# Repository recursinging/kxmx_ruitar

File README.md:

# kxmx_ruitar

A guitar shaped MIDI/OSC instrument

## The Idea

The goal of this project is pretty simple; Take the general functionality of your typical MIDI keyboard or control surface and implement it (robustly, and with low latency) in the form factor of a guitar.  The motivation is a a little less straightforward. Three things:

1. I wanted to wear it on stage while maintaining the freedom to move about.  
1. I wanted to make it myself.
1. It didn't want to spend a fortune.

I like the form factor of a guitar because it can look quite traditional in a rock band context, but upon closer inspection is clearly not.  This reflects my taste in music, superficially recognizable, but substantially deviant.  While I can play the guitar, I didn't feel it necessary that a functional [guitar be augmented](http://lividinstruments.com/products/guitar-wing/) with MIDI controller capabilities, unless the two can be [seamlessly combined](https://www.rorguitars.com/products/expressiv-midi-pro). This is primarily because my single-threaded brain just cannot effectively handle playing an instrument well, while controlling other parameters. 

Because a guitar hangs down in front of you, facing out, visual controls and feedback are pretty useless.  [A touch screen on the front of the guitar](https://misa-digital.myshopify.com/products/tri-bass) for example, is effectively a touch-pad for the player and a light show for the audience. Therefore I am mostly interested in tactile type sensors which can be blindly interacted with.

The DIY approach is simply an excuse to get lost in the details of interesting technical challenges instead of practicing, or composing actual music. 

Regarding limiting cost... Yeah, anyone who has ever attempted a DIY project like this knows it's actually BS. There is no competing with the economies of scale that a market product has. We DIYers like to trick ourselves by spreading the costs into tiny chunks, over many months. But, I consider the premium an investment in enjoyment and the knowledge gained along the way. So that's how it ended up here.  

## The (current) BOM

* 1 [Teensy 3.6](https://www.pjrc.com/store/teensy36.html) with SD card
* 1 Junk electric guitar, or similarly shaped object.
* 4 500mm [ThinPot](http://www.spectrasymbol.com/product/thinpot/) Membrane Potentiometers (Strings)
* 4 38x38mm [FSR](https://www.interlinkelectronics.com/fsr-406) Pressure Sensors (Pads)
* 1 [Joystick](https://www.adafruit.com/product/444)
* 4 45mm [Slider Potentiometers](https://www.digikey.com/product-detail/en/tt-electronics-bi/PS45-21PC3BR10K/987-1409-ND/2620678) (Faders)
* 4 [LED Buttons](https://www.sparkfun.com/products/10442) (Toggles)
* 1 [SSD1306 64x32 OLED display](https://www.adafruit.com/product/326)
* A diverse set of 0805 SMD resistors and capacitors
* Bits and Bobs (proto board, hookup wire, solder, tape, velcro, etc.)

(With Optional Headstock)

* 1 [Teensy LC](https://www.pjrc.com/teensy/teensyLC.html)
* 4 [RGB LED Rotary Encoders](https://www.sparkfun.com/products/10982)
* 1 [ADXL345 3 Axis Accelerometer](https://www.sparkfun.com/datasheets/Sensors/Accelerometer/ADXL345.pdf) (Accel)
* 1 [TLC5940 PWM Controller](http://www.ti.com/lit/ds/symlink/tlc5940.pdf)
* A diverse set of 0805 SMD resistors and capacitors
* [The ruitar-head PCB]()

## The Build

The guitar used was a junk no-name electric.  I hollowed out from the front of the body with an oscillating multi-tool and a wood blade, leaving space for the FSRs.  Because the body is plywood, it was pretty easy to remove the bulk of the material.  I spray-painted everything black and carpeted the inside with adhesive Velcro strips (loop side). This has been quite helpful for cable management and general experimentation.  Just put some hook Velcro to the bottom of a breadboard and stick it in there. Need a USB Hub? Raspberry Pi? Velcro!

The FSRs are attached with some double sided foam tape which holds them solidly in place and gives them a little bit of padding, which is good when you are banging on them with your knuckles.  The little thumb joystick is mounted in the body with hot glue, and wired through a hole bored into the body cavity. The joystick is meant to be moved with the palm of your hand, allowing you to modulate parameters while tapping on the FSRs... In practice, little thumb joysticks like that are junk, they have too little travel to introduce any decent dynamic.  I am actively looking for an alternative, larger joystick with more travel.

The first prototype was done using breadboards and an Arduino Mega2650 clone.  When it was finally functional, I found the latency to be unacceptable, the breadboard connections were fragile and problematic,and I also found it lacking interface components.  So, I swapped the Mega2650 for a Teensy 3.6, soldered all the connections using some protoboard, and added the four faders plus four LED buttons. The result is this new prototype module. I'm designing a PCB which will replace this.

There are USB-A and RJ-45 jacks to the side using some nice, locking Neutrik jacks.  Because the Teensy's advanced USB capabilities, there is only USB IO at the moment.  The unused RJ-45 is for some future ideas.

There is an SSD1306 64x32 OLED display mounted to the side of the body of the guitar. I simply flattened a little part of the edge with a belt sander, and drilled a hole into the body cavity for the wires. A 3d-printed protective case surrounding the display would be useful.

There is a cover for the body cavity I cut out of plastic to hide the unruly guts (although the aesthetics of the exposed internals are also appealing).  Note that this photo was also taken before the faders and buttons were added, which means that the cover, in that form is not currently usable, but I'm still unsure about the final positions of those components anyhow. 

The neck was a huge pain. Removing the truss rod required brute force, but afterward I had a cable channel through which I am able to pull wires from the body, up to the head stock. In order to adhere the membrane potentiometers, I needed to flatten the fingerboard. I didn't have any good ideas how, so I ended up just sanding the frets down with a belt sander. There are no photos of this process because I was too busy cursing. The result is OK but if you want to try this yourself, I'd recommend looking for a cheap neck without a fingerboard (although I was unable to find one). Once flattened I attached the membrane potentiometers and covered them with a layer of electrical tape.  I then laid some straightened 14 gauge solid core wire down the middle of each sensor, and put another layer of tape on top.  This provides some tactile feedback as to where the sensors actually are, and really helps the play-ability.  The position tracking through the wire is excellent.

[The headstock](https://github.com/recursinging/kxmx_ruitar/tree/master/ruitar-head) is a separate entity with its own microcontroller, a ([Teensy LC](https://www.pjrc.com/teensy/teensyLC.html)) acting as an I²C slave device.  It is attached to the headstock of a guitar. I've connected it to the body module with wires pulled through the neck of the guitar.  I removed all the tuning hardware and screwed it directly to the headstock.  Currently, it is quite exposed and fragile.  I'd like to design a 3d printed protective cover for it.

Put all together and you have a ruitar!

## Schematics

TODO

## Firmware

Because the headstock and body have their own microcontrollers, this project is split into two sections, the *ruitar-body* and the *ruitar-head*.  The directory layouts of both projects are currently set up for [platformio](https://platformio.org/), it works. It's not bad.

### [ruitar-body](https://github.com/recursinging/kxmx_ruitar/tree/master/ruitar-head)

The ruitar-body is the core of the instrument, effectively a variety of sensors attached to a microcontroller (a [Teensy 3.6](https://www.pjrc.com/store/teensy36.html)).  These sensors are sampled via the microcontroller ADCs, the values are calculated and, if appropriate, MIDI and OSC messages are sent out. (currently via USB to a PC).

The logic controlling when and what messages to send is configurable by a INI style text files on an SD card. These files can be considered "Presets" and can be copied, modified, renamed, and saved to the SD card.  

TODO - Include config file example

I had plans to make presets configurable through the sensors, and OLED display, but I found the OSC GUI much easier and more powerful, so the OLED display is currently relegated to display some basic debugging info at the moment.  Perhaps there is a better use for it, or the SPI pins it is occupying?

Presets can also be edited via OSC using [the GUI definition](https://github.com/recursinging/kxmx_ruitar/blob/master/osc-gui.json) for [Open Stage Control](https://osc.ammd.net/)

The default configuration is for it to behave a bit like a real guitar. Pressing a position on a "string" (0-3) determines the pitch of the note, while triggering the note on state, and its velocity is determined by pressure detected at the associated (0-3) "pad".  The faders, and toggles emit CC messages, and the joystick can emit CC and pitch bend messages. Sensor values received from the head (accelerometer, encoders) can also be configured to emit MIDI CC messages.

### [ruitar-head](https://github.com/recursinging/kxmx_ruitar/tree/master/ruitar-head)

The ruitar-head is set of sensors attached to a microcontroller ([Teensy LC](https://www.pjrc.com/teensy/teensyLC.html)) acting as an I²C slave device. The firmware provides a set of read-only registers which can be read to obtain the accelerometer, and encoder values.  Additionally the state of the RGB LEDs can be polled and changed by a set of read-write registers.

## TODOs

Things that still need to be done, but are incomplete.

- [ ] Design a PCB for the body
- [ ] Fix broken I²C communication between body and head
- [ ] Implement the OSC GUI parameter config
- [ ] Implement the OSC GUI preset copy/rename/save functions
- [ ] Implement a useful MIDI emitter for the accelerometer data
- [ ] Design some 3d printable protective parts for the exposed bits.
- [ ] Provide better descriptions, code comments, build docs, pics, etc

## Future Feature Ideas

A few ideas I've been batting around:

### Synth! 

The Teensy 3.6 is laughing at the current workload.  There is plenty of capacity to implement a digital synth, and the Teensy Audio library is amazing.  I've already started this, but ran into a couple of problems:

* An I²S codec needs quite a few pins, many of which are currently being used
* USB audio is not really an option if you already have a USB audio interface.

Nothing insurmountable, I'd like to make this happen if I find the time.

### Ethernet (or WiFi)

At the moment OSC is provided over SLIP encoded Serial. This works, but is a kludge requiring [a bridge program](https://github.com/recursinging/kxmx_trestle) to get the UDP packets that all the OSC clients expect.

There is a Neutrik RJ-45 jack built into the body of the ruitar,  I could provide power over the unused pairs assuming 100-BASE-T.  But without the USB cable I would loose all the USB* devices the Teensy can emulate, which would be a bummer. 

Alternatively I could send the SLIP serial to an ESP32 and broadcast the OSC packets via WiFi, not sure about the latency though. 

### Membrane Potentiometer Alternatives

The kxmx_ruitar is *really* hard to play.  Tracking on the "strings" is not bad, but the lack of any tactile feedback along them makes it difficult to get a position reference. Anyway, since MIDI notes are discrete, all the position data the pot and ADC could provide gets quantized to the configured 20 note range anyway... They might as well be buttons, right?

## Inspiration, Ideas, and Prior Art

Here's a list of products and projects from which I have gathered ideas:

* [Misa Digital Tri-Bass](https://misa-digital.myshopify.com/products/tri-bass)
* [Starr Labs Z-Tars](https://www.starrlabs.com/product/z6s/)
* [Expressiv MIDI Pro](https://www.rorguitars.com/products/expressiv-midi-pro)
* [Alesis Vortex](https://www.alesis.com/products/view2/vortex-wireless-2)

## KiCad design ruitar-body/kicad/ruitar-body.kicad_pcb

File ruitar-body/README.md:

# kxmx_ruitar_body

The body module of the kxmx_ruitar

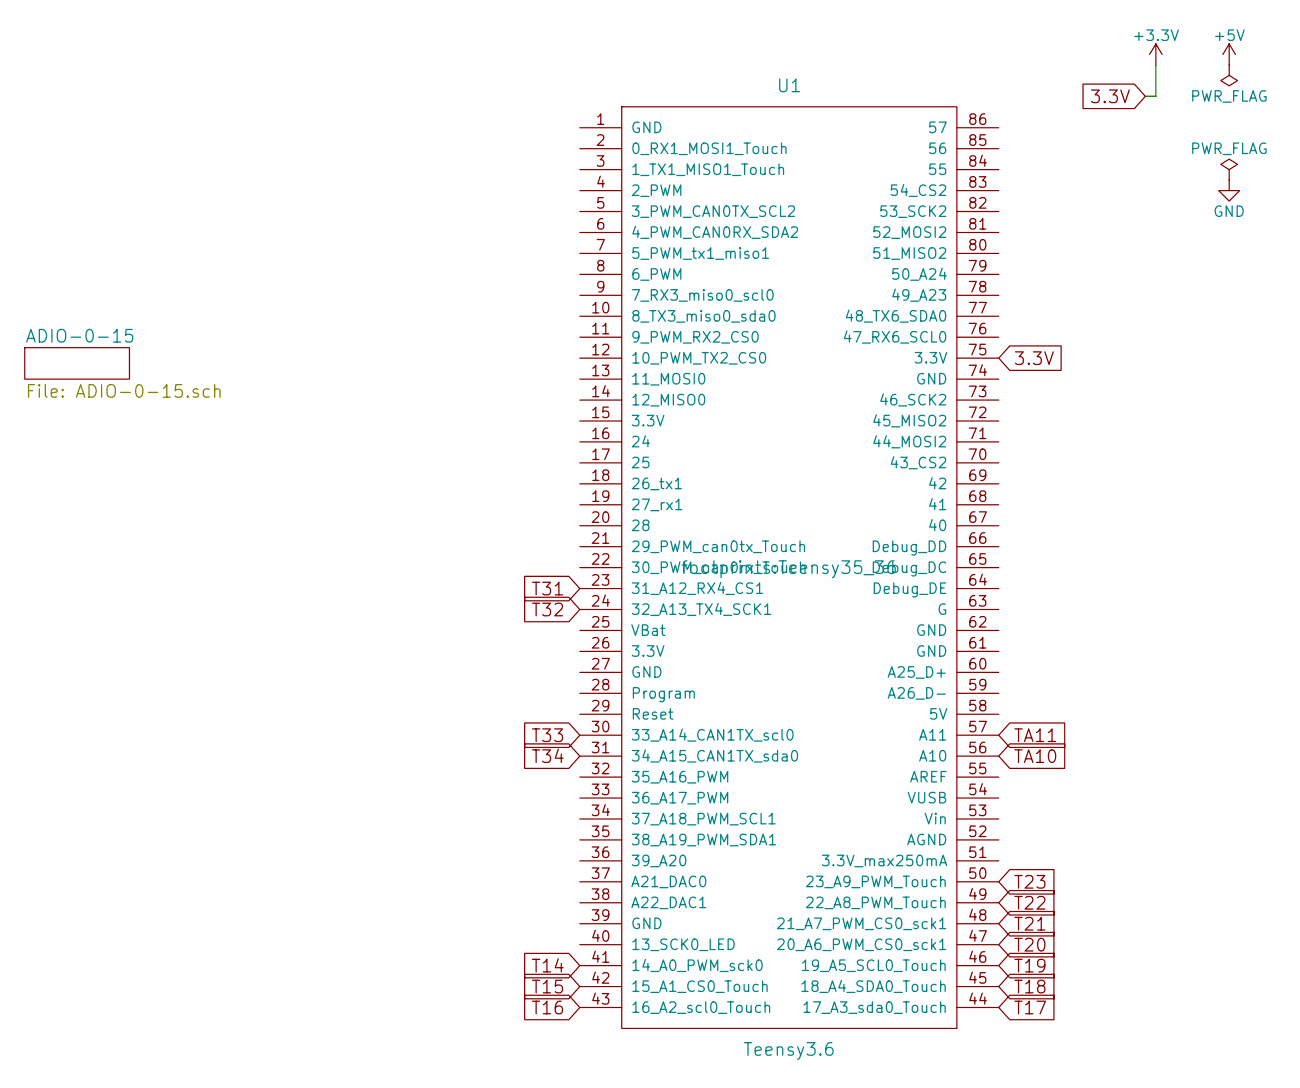
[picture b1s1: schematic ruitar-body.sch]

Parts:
U1: Teensy3.6; Teensy35_36

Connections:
3.3V: U1.75 (3.3V); also elsewhere on the board
T14: U1.41 (14_A0_PWM_sck0); also elsewhere on the board
T15: U1.42 (15_A1_CS0_Touch); also elsewhere on the board
T16: U1.43 (16_A2_scl0_Touch); also elsewhere on the board
T17: U1.44 (17_A3_sda0_Touch); also elsewhere on the board
T18: U1.45 (18_A4_SDA0_Touch); also elsewhere on the board
T19: U1.46 (19_A5_SCL0_Touch); also elsewhere on the board
T20: U1.47 (20_A6_PWM_CS0_sck1); also elsewhere on the board
T21: U1.48 (21_A7_PWM_CS0_sck1); also elsewhere on the board
T22: U1.49 (22_A8_PWM_Touch); also elsewhere on the board
T23: U1.50 (23_A9_PWM_Touch); also elsewhere on the board
T31: U1.23 (31_A12_RX4_CS1); also elsewhere on the board
T32: U1.24 (32_A13_TX4_SCK1); also elsewhere on the board
T33: U1.30 (33_A14_CAN1TX_scl0); also elsewhere on the board
T34: U1.31 (34_A15_CAN1TX_sda0); also elsewhere on the board
TA10: U1.56 (A10); also elsewhere on the board
TA11: U1.57 (A11); also elsewhere on the board

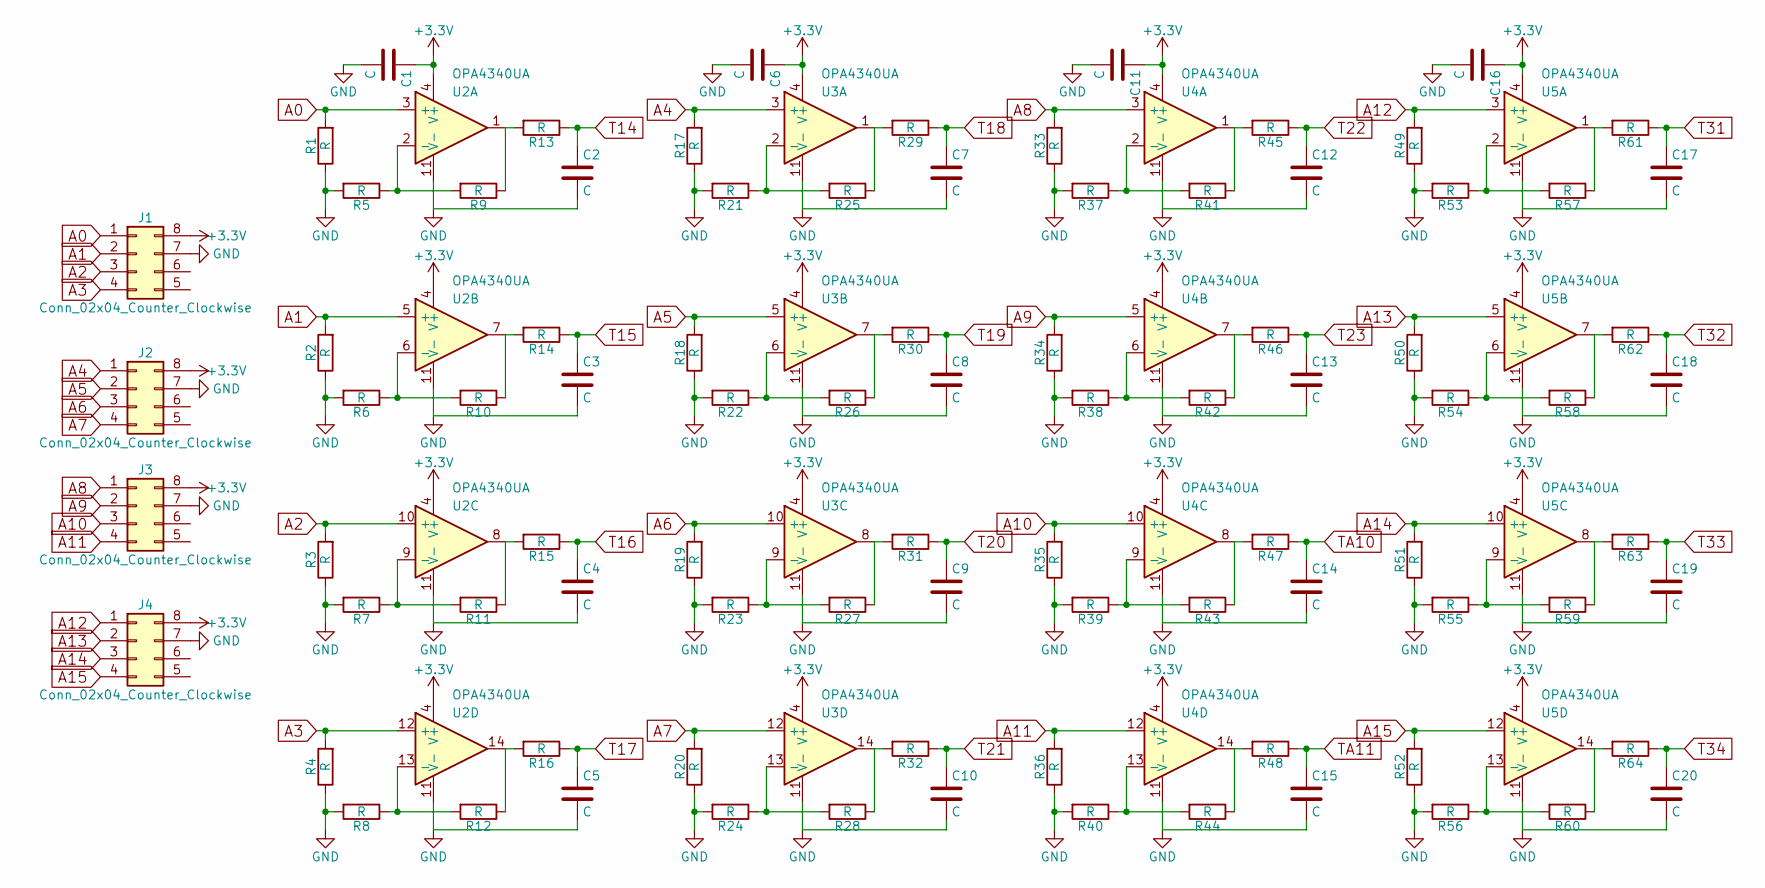
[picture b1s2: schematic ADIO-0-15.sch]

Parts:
C1, C2, C3, C4, C5, C6, C7, C8, C9, C10, C11, C12, C13, C14, C15, C16, C17, C18, C19, C20: C; C_0805
J1, J2, J3, J4: Conn_02x04_Counter_Clockwise; RJ45_8
R1, R2, R3, R4, R5, R6, R7, R8, R9, R10, R11, R12, R13, R14, R15, R16, R17, R18, R19, R20, R21, R22, R23, R24, R25, R26, R27, R28, R29, R30, R31, R32, R33, R34, R35, R36, R37, R38, R39, R40, R41, R42, R43, R44, R45, R46, R47, R48, R49, R50, R51, R52, R53, R54, R55, R56, R57, R58, R59, R60, R61, R62, R63, R64: R; R_0805
U2, U3, U4, U5: OPA4340UA; SOIC-14_3.9x8.7mm_Pitch1.27mm

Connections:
3.3V: C1.1, C6.1, C11.1, C16.1, J1.8, J2.8, J3.8, J4.8, U2.4 (V+), U3.4 (V+), U4.4 (V+), U5.4 (V+); also elsewhere on the board
A0: J1.1, R1.2, U2.3 (+)
A1: J1.2, R2.2, U2.5 (+)
A2: J1.3, R3.2, U2.10 (+)
A3: J1.4, R4.2, U2.12 (+)
A4: J2.1, R17.2, U3.3 (+)
A5: J2.2, R18.2, U3.5 (+)
A6: J2.3, R19.2, U3.10 (+)
A7: J2.4, R20.2, U3.12 (+)
A8: J3.1, R33.2, U4.3 (+)
A9: J3.2, R34.2, U4.5 (+)
A10: J3.3, R35.2, U4.10 (+)
A11: J3.4, R36.2, U4.12 (+)
A12: J4.1, R49.2, U5.3 (+)
A13: J4.2, R50.2, U5.5 (+)
A14: J4.3, R51.2, U5.10 (+)
A15: J4.4, R52.2, U5.12 (+)
GND: C1.2, C2.2, C3.2, C4.2, C5.2, C6.2, C7.2, C8.2, C9.2, C10.2, C11.2, C12.2, C13.2, C14.2, C15.2, C16.2, C17.2, C18.2, C19.2, C20.2, J1.7, J2.7, J3.7, J4.7, R1.1, R2.1, R3.1, R4.1, R5.2, R6.2, R7.2, R8.2, R17.1, R18.1, R19.1, R20.1, R21.2, R22.2, R23.2, R24.2, R33.1, R34.1, R35.1, R36.1, R37.2, R38.2, R39.2, R40.2, R49.1, R50.1, R51.1, R52.1, R53.2, R54.2, R55.2, R56.2, U2.11 (V-), U3.11 (V-), U4.11 (V-), U5.11 (V-)
unnamed: R5.1, R9.2, U2.2 (-)
unnamed: R10.1, R14.2, U2.7
unnamed: R6.1, R10.2, U2.6 (-)
unnamed: R11.1, R15.2, U2.8
unnamed: R7.1, R11.2, U2.9 (-)
unnamed: R12.1, R16.2, U2.14
unnamed: R8.1, R12.2, U2.13 (-)
unnamed: R9.1, R13.2, U2.1
unnamed: R21.1, R25.2, U3.2 (-)
unnamed: R22.1, R26.2, U3.6 (-)
unnamed: R23.1, R27.2, U3.9 (-)
unnamed: R24.1, R28.2, U3.13 (-)
unnamed: R25.1, R29.2, U3.1
unnamed: R26.1, R30.2, U3.7
unnamed: R27.1, R31.2, U3.8
unnamed: R28.1, R32.2, U3.14
unnamed: R37.1, R41.2, U4.2 (-)
unnamed: R38.1, R42.2, U4.6 (-)
unnamed: R39.1, R43.2, U4.9 (-)
unnamed: R40.1, R44.2, U4.13 (-)
unnamed: R41.1, R45.2, U4.1
unnamed: R42.1, R46.2, U4.7
unnamed: R43.1, R47.2, U4.8
unnamed: R44.1, R48.2, U4.14
unnamed: R53.1, R57.2, U5.2 (-)
unnamed: R54.1, R58.2, U5.6 (-)
unnamed: R55.1, R59.2, U5.9 (-)
unnamed: R56.1, R60.2, U5.13 (-)
unnamed: R57.1, R61.2, U5.1
unnamed: R58.1, R62.2, U5.7
unnamed: R59.1, R63.2, U5.8
unnamed: R60.1, R64.2, U5.14
T14: C2.1, R13.1; also elsewhere on the board
T15: C3.1, R14.1; also elsewhere on the board
T16: C4.1, R15.1; also elsewhere on the board
T17: C5.1, R16.1; also elsewhere on the board
T18: C7.1, R29.1; also elsewhere on the board
T19: C8.1, R30.1; also elsewhere on the board
T20: C9.1, R31.1; also elsewhere on the board
T21: C10.1, R32.1; also elsewhere on the board
T22: C12.1, R45.1; also elsewhere on the board
T23: C13.1, R46.1; also elsewhere on the board
T31: C17.1, R61.1; also elsewhere on the board
T32: C18.1, R62.1; also elsewhere on the board
T33: C19.1, R63.1; also elsewhere on the board
T34: C20.1, R64.1; also elsewhere on the board
TA10: C14.1, R47.1; also elsewhere on the board
TA11: C15.1, R48.1; also elsewhere on the board

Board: 2 copper layers, 93 parts (0 on the bottom side), 66 nets, no tracks yet.

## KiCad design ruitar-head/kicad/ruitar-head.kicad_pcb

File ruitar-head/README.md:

# kxmx_ruitar_head

The headstock module of the kxmx_ruitar

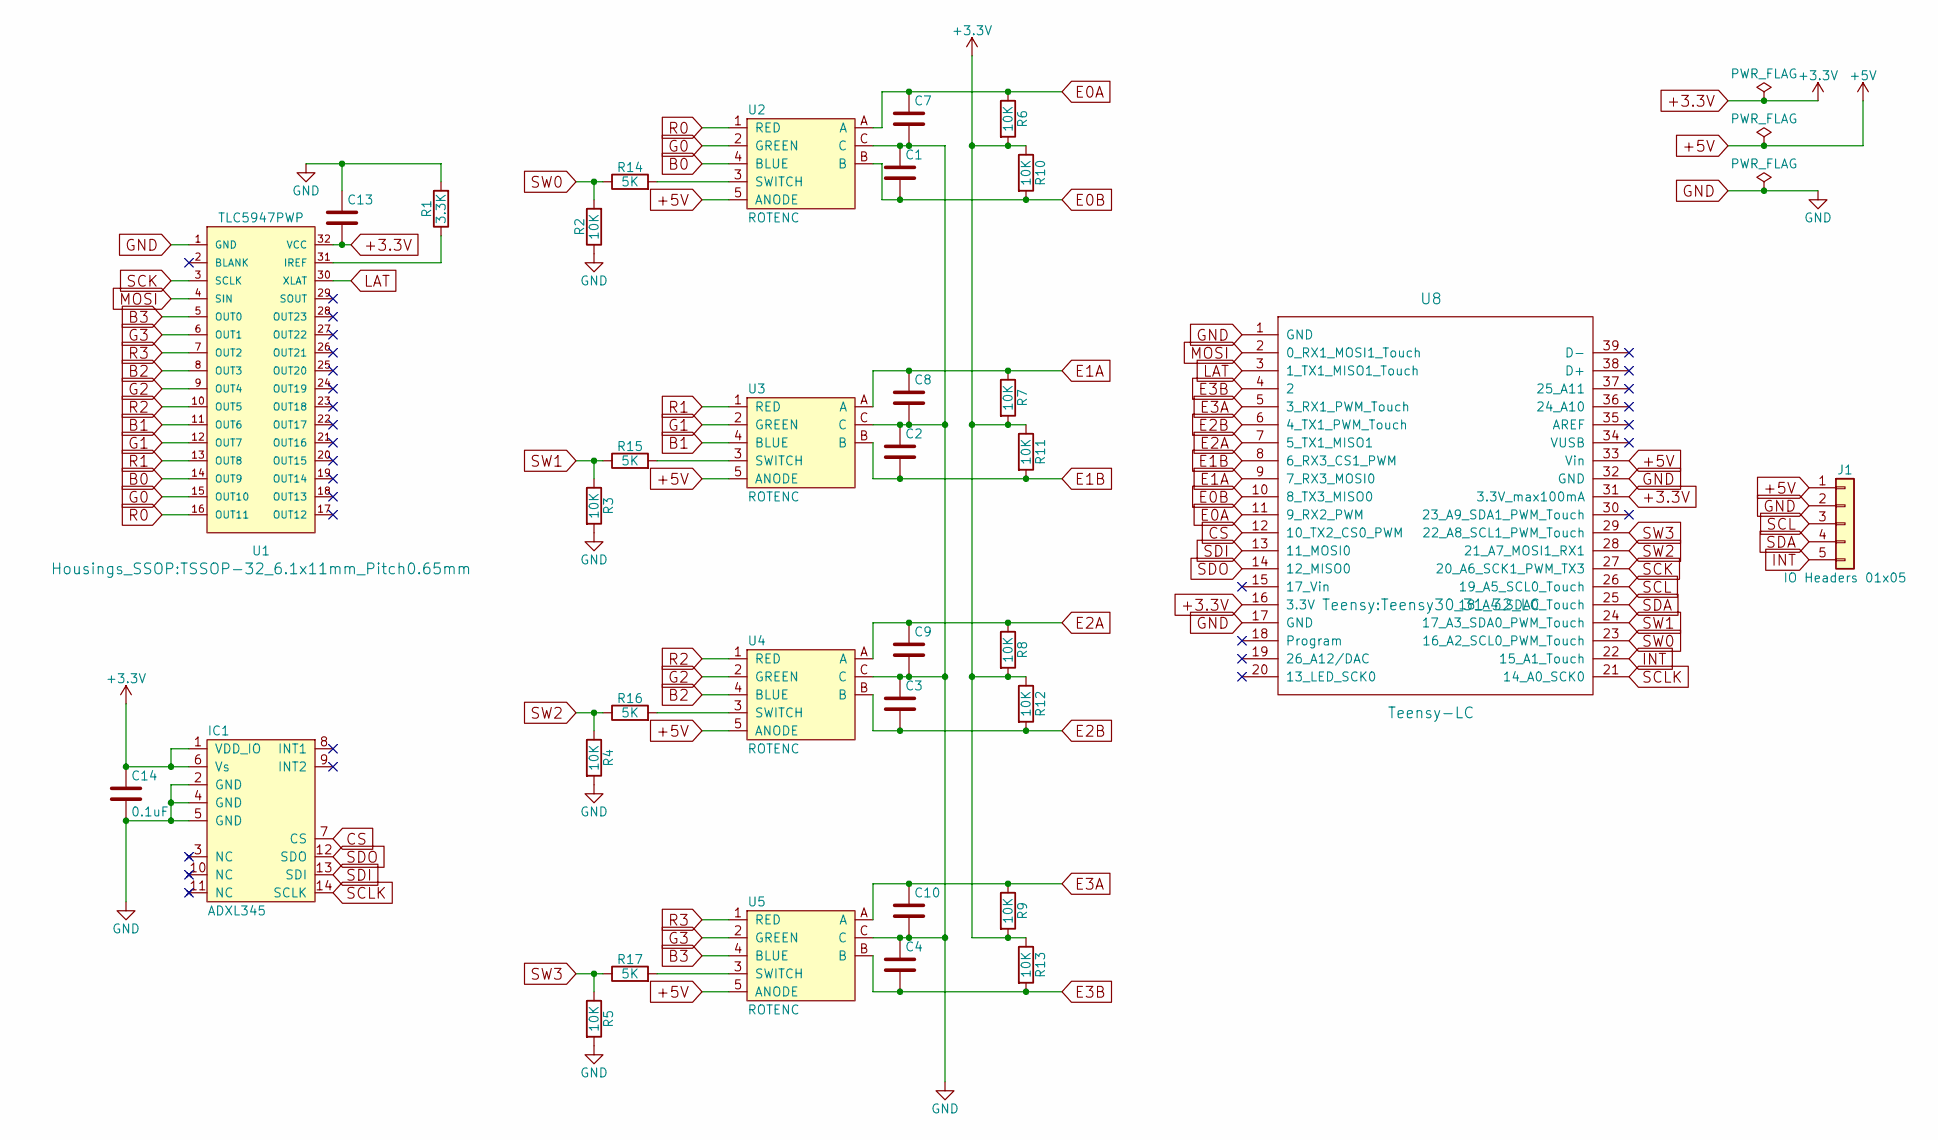
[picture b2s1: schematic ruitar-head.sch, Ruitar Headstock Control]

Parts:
C1, C2, C3, C4, C7, C8, C9, C10, C13, C14: 0.1uF; C_0805_HandSoldering
IC1: ADXL345; ADXL3x5; Farnell 1853935
J1: IO Headers 01x05; Pin_Header_Straight_1x05_Pitch2.54mm
R1: 3.3K; R_0805_HandSoldering
R2, R3, R4, R5, R6, R7, R8, R9, R10, R11, R12, R13: 10K; R_0805_HandSoldering
R14, R15, R16, R17: 5K; R_0805_HandSoldering
U1: TLC5947PWP; TSSOP-32_6.1x11mm_Pitch0.65mm
U2, U3, U4, U5: ROTENC; SF_ROTENC
U8: Teensy-LC; Teensy30_31_32_LC

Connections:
+3.3V: C13.2, C14.1, IC1.1 (VDD_IO), IC1.6 (Vs), R6.2, R7.2, R8.2, R9.2, R10.1, R11.1, R12.1, R13.1, U1.32 (VCC), U8.16 (3.3V), U8.31 (3.3V_max100mA)
+5V: J1.1, U2.5 (ANODE), U3.5 (ANODE), U4.5 (ANODE), U5.5 (ANODE), U8.33 (Vin)
B0: U1.14 (OUT9), U2.4 (BLUE)
B1: U1.11 (OUT6), U3.4 (BLUE)
B2: U1.8 (OUT3), U4.4 (BLUE)
B3: U1.5 (OUT0), U5.4 (BLUE)
CS: IC1.7 (CS), U8.12 (10_TX2_CS0_PWM)
E0A: C7.1, R6.1, U2.A, U8.11 (9_RX2_PWM)
E0B: C1.2, R10.2, U2.B, U8.10 (8_TX3_MISO0)
E1A: C8.1, R7.1, U3.A, U8.9 (7_RX3_MOSI0)
E1B: C2.2, R11.2, U3.B, U8.8 (6_RX3_CS1_PWM)
E2A: C9.1, R8.1, U4.A, U8.7 (5_TX1_MISO1)
E2B: C3.2, R12.2, U4.B, U8.6 (4_TX1_PWM_Touch)
E3A: C10.1, R9.1, U5.A, U8.5 (3_RX1_PWM_Touch)
E3B: C4.2, R13.2, U5.B, U8.4 (2)
G0: U1.15 (OUT10), U2.2 (GREEN)
G1: U1.12 (OUT7), U3.2 (GREEN)
G2: U1.9 (OUT4), U4.2 (GREEN)
G3: U1.6 (OUT1), U5.2 (GREEN)
GND: C1.1, C2.1, C3.1, C4.1, C7.2, C8.2, C9.2, C10.2, C13.1, C14.2, IC1.2 (GND), IC1.4 (GND), IC1.5 (GND), J1.2, R1.2, R2.1, R3.2, R4.2, R5.2, U1.1 (GND), U2.C, U3.C, U4.C, U5.C, U8.1 (GND), U8.17 (GND), U8.32 (GND)
INT: J1.5, U8.22 (15_A1_Touch)
LAT: U1.30 (XLAT), U8.3 (1_TX1_MISO1_Touch)
MOSI: U1.4 (SIN), U8.2 (0_RX1_MOSI1_Touch)
unnamed: R1.1, U1.31 (IREF)
unnamed: R14.2, U2.3 (SWITCH)
unnamed: R15.2, U3.3 (SWITCH)
unnamed: R16.2, U4.3 (SWITCH)
unnamed: R17.2, U5.3 (SWITCH)
R0: U1.16 (OUT11), U2.1 (RED)
R1: U1.13 (OUT8), U3.1 (RED)
R2: U1.10 (OUT5), U4.1 (RED)
R3: U1.7 (OUT2), U5.1 (RED)
SCK: U1.3 (SCLK), U8.27 (20_A6_SCK1_PWM_TX3)
SCL: J1.3, U8.26 (19_A5_SCL0_Touch)
SCLK: IC1.14 (SCLK), U8.21 (14_A0_SCK0)
SDA: J1.4, U8.25 (18_A4_SDA0_Touch)
SDI: IC1.13 (SDI), U8.13 (11_MOSI0)
SDO: IC1.12 (SDO), U8.14 (12_MISO0)
SW0: R2.2, R14.1, U8.23 (16_A2_SCL0_PWM_Touch)
SW1: R3.1, R15.1, U8.24 (17_A3_SDA0_PWM_Touch)
SW2: R4.1, R16.1, U8.28 (21_A7_MOSI1_RX1)
SW3: R5.1, R17.1, U8.29 (22_A8_SCL1_PWM_Touch)

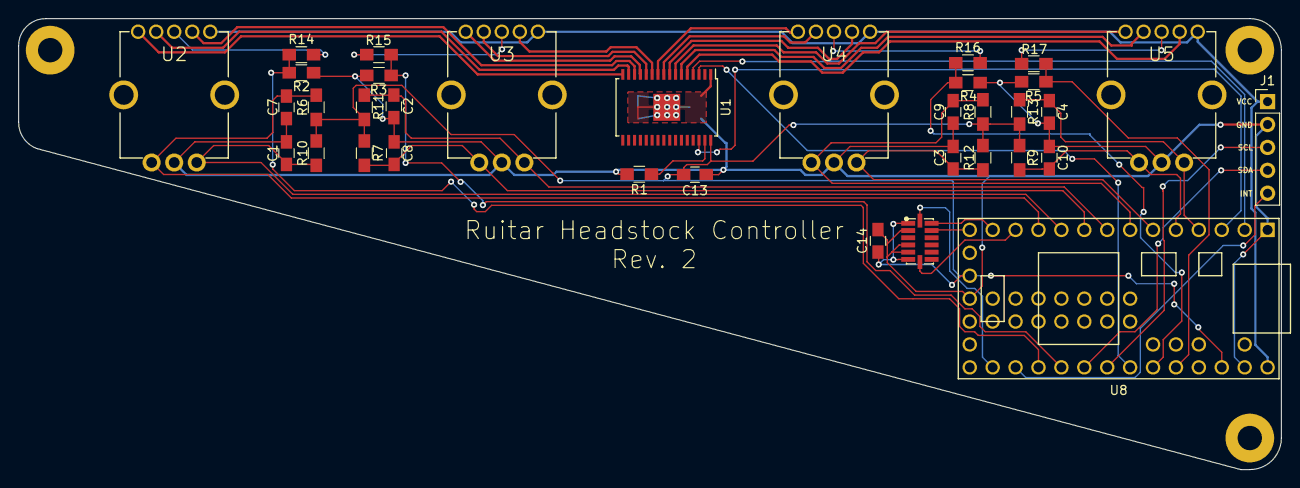
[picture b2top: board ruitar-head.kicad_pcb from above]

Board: 2 copper layers, 140.0 x 50.0 mm, 35 parts (0 on the bottom side), 42 nets.

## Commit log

2018-08-31 Restructure. Rename. Document.
2018-09-06 Remove and ignore some local vscode configs
2018-09-06 Start adding some project documentation
2018-09-06 Add some documentation images
2018-09-06 Linked some of the doc images in the README
2018-09-06 Add GUI screenshot to the docs
2018-09-06 The GUI screenshot is a png not a jpg.
2018-09-07 Restructure the README a bit
2018-09-10 Adjust a few default MIDI settings
2018-10-31 Add the base for a headstock protective case
2018-11-19 Testing the MIDI input handling at tonights practice session
2019-09-16 Simplify a few things to make debugging a wiring problem easier...
2019-09-24 Some minor changes for experimenting with the poly 2
